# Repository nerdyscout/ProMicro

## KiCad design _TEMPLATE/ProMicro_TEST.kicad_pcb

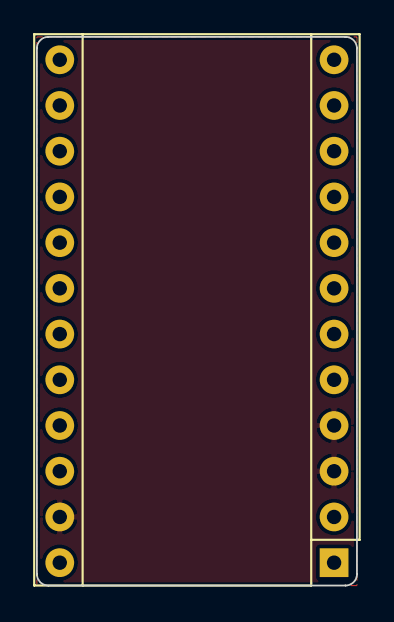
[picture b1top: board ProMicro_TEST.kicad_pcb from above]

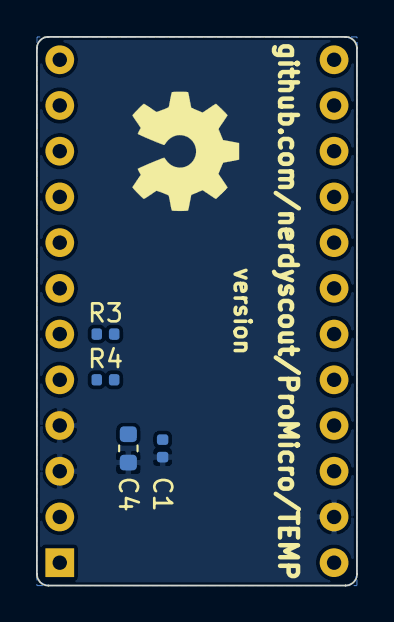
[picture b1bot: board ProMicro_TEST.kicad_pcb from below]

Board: 2 copper layers, 17.8 x 30.5 mm, 6 parts (5 on the bottom side), 4 nets, no tracks yet.

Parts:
A1: Sparkfun_Pro_Micro
C1: 100n; C_0402_1005Metric
C4: 10µ; C_0603_1608Metric
LOGO1: Logo_Open_Hardware_Small; OSHW-Symbol_6.7x6mm_SilkScreen
R3, R4: 4k7; R_0402_1005Metric

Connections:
+3V3: A1.21, C1.1, C4.1, R3.2, R4.2
GND: A1.3, A1.4, A1.23, C1.2, C4.2
SCL: A1.6, R3.1
SDA: A1.5, R4.1

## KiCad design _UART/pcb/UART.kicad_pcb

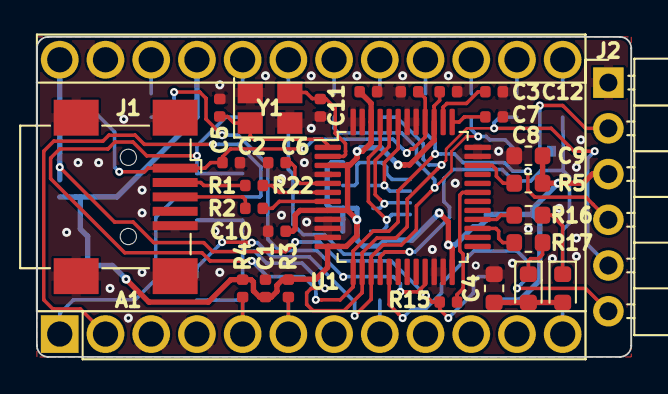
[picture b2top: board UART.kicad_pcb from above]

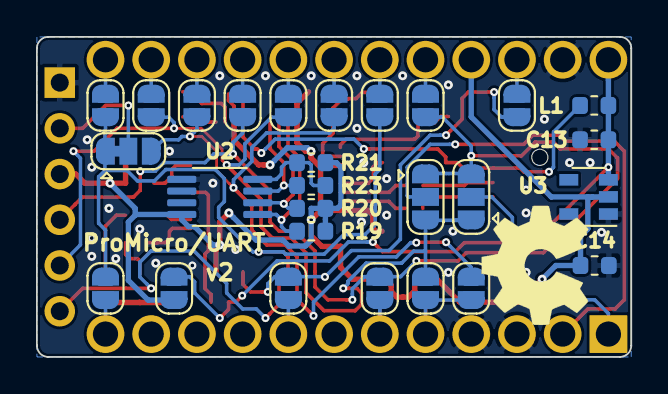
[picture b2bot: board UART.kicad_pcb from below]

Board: 4 copper layers, 33.0 x 17.8 mm, 56 parts (28 on the bottom side), 45 nets.

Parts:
A1: Sparkfun_Pro_Micro_3V3; Sparkfun_Pro_Micro
C1, C3, C7, C8, C10, C11, C12: 100n; C_0402_1005Metric
C2: 4.7µ; C_0402_1005Metric
C4: 10µ; C_0603_1608Metric
C5, C6: 27p; C_0402_1005Metric
C9: 4.7µ; R_0603_1608Metric
C13, C14: 1µ; C_0603_1608Metric
D1: TX; LED_0603_1608Metric
D2: RX; LED_0603_1608Metric
J1: USB_B_Mini; USB_Mini-B_Wuerth_65100516121_Horizontal
J2: Conn_01x06; PinHeader_1x06_P2.54mm_Horizontal
JP1, JP2, JP3, JP4, JP5, JP6, JP7, JP8, JP9, JP12, JP13, JP14, JP15, JP17, JP18: Jumper_NO_Small; SolderJumper-2_P1.3mm_Open_RoundedPad1.0x1.5mm
JP10, JP11: Jumper_3_Bridged12; SolderJumper-3_P1.3mm_Open_RoundedPad1.0x1.5mm
JP16: Jumper_3_Bridged12; SolderJumper-3_P1.3mm_Bridged12_RoundedPad1.0x1.5mm
L1: 0; L_0603_1608Metric
LOGO1: Logo_Open_Hardware_Small; OSHW-Symbol_6.7x6mm_SilkScreen
R1, R2: 22; R_0402_1005Metric
R3, R4: 4k7; R_0402_1005Metric
R5: 1k; R_0603_1608Metric
R15: 39k; R_0402_1005Metric
R16, R17: 220; R_0603_1608Metric
R19, R20, R21: 10k; R_0603_1608Metric
R22: 12k; R_0402_1005Metric
R23: 2k; R_0603_1608Metric
U1: FT232H; LQFP-48_7x7mm_P0.5mm
U2: 93CxxB; MSOP-8_3x3mm_P0.65mm
U3: AZ1117-3.3; SOT-23-5
Y1: 12MHz; Crystal_SMD_3225-4Pin_3.2x2.5mm

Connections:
+3V3: A1.21, C1.1, C4.1, C9.1, C10.2, C11.2, C12.1, C14.1, D1.2, D2.2, J2.3, JP18.2, R3.2, R4.2, R5.2, R19.2, R20.2, R21.2, U1.3, U1.8, U1.12, U1.24, U1.39, U1.46, U2.8, U3.2
+5V: A1.24, C13.1, JP18.1, L1.1, R15.2, U3.3
/CIPO: A1.15, JP3.2
/COPI: A1.14, JP2.2
/CS0: A1.13, JP5.2
/CS1: A1.12, JP4.2
/EECLK: R20.1, U1.44, U2.2
/EECS: R19.1, U1.45, U2.1
/EEDAT: R23.1, U1.43, U2.3
/PWM: A1.8, JP12.2
/RXD: A1.1, JP10.2
/SCK: A1.16, JP1.2
/SCL: A1.6, JP15.2, R3.1
/SDA: A1.5, JP13.2, JP14.2, R4.1
/TCK: A1.20, JP6.2
/TDI: A1.17, JP7.2
/TDO: A1.18, JP8.2
/TMS: A1.19, JP9.2
/TXD: A1.2, JP11.2
/~RST: A1.22, JP17.2
ACBUS0: JP12.1, JP17.1, U1.21
ADBUS0: J2.4, JP1.1, JP6.1, JP10.3, JP11.1, JP15.1, U1.13
ADBUS1: J2.5, JP2.1, JP7.1, JP10.1, JP11.3, JP13.1, U1.14
ADBUS2: JP3.1, JP8.1, JP14.1, JP16.3, U1.15
ADBUS3: JP4.1, JP5.1, JP9.1, JP16.1, U1.16
ADBUS4: J2.6, U1.17
GND: A1.3, A1.4, A1.23, C1.2, C2.2, C3.2, C4.2, C5.2, C6.2, C7.2, C8.2, C9.2, C10.1, C11.1, C12.2, C13.2, C14.2, J1.5, J1.6, J2.1, R22.2, U1.4, U1.9, U1.10, U1.11, U1.22, U1.23, U1.35, U1.36, U1.41, U1.42, U1.47, U1.48, U2.5, U3.1, Y1.2, Y1.4
unnamed: C2.1, C3.1, J1.1, L1.2, U1.40
unnamed: C5.1, U1.1, Y1.1
unnamed: C6.1, U1.2, Y1.3
unnamed: C7.1, U1.38
unnamed: C8.1, U1.37
unnamed: D1.1, R16.2
unnamed: D2.1, R17.2
unnamed: J1.2, R1.2
unnamed: J1.3, R2.2
unnamed: J2.2, JP16.2
unnamed: R1.1, U1.6
unnamed: R2.1, U1.7
unnamed: R5.1, U1.34
unnamed: R21.1, R23.2, U2.4
unnamed: R22.1, U1.5
PWRSAV: R15.1, U1.31
RXLED: R17.1, U1.27
TXLED: R16.1, U1.28

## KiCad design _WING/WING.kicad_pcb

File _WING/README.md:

# ProMicro_WING

## Documentation 
All files can be found on [Github](https://github.com/nerdyscout/ProMicro/tree/master/WING).

### Schematic

### BoM
  * [interactiveHTMLBoM](https://nerdyscout.github.io/ProMicro/WING/docs/bom/WING-ibom.html)
  * [octopart](pcb/docs/bom/WING-bom_octopart.csv)

## Hardware 
### Layout

### Gerbers
can be found within the Github [repository](pcb/gerbers).

## external
### Links
  * [hackaday.io](https://hackaday.io/project/171898-promicro)

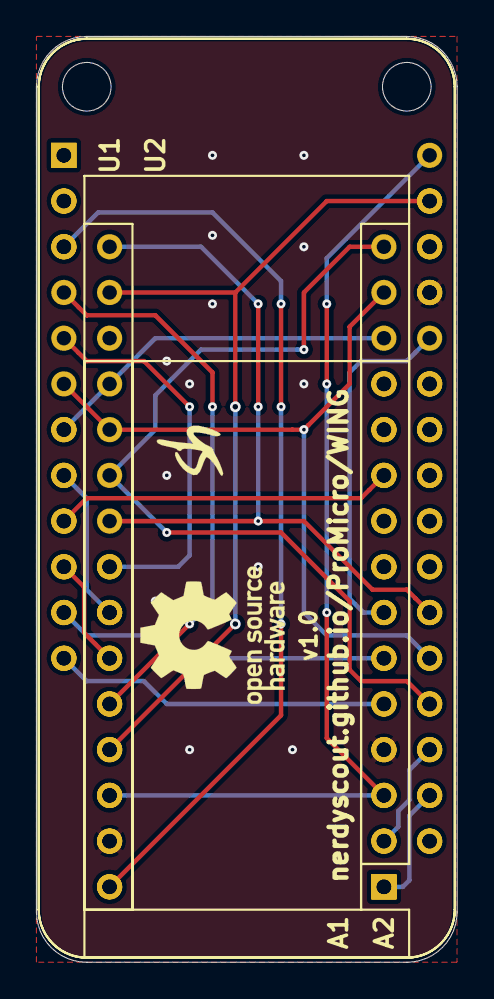
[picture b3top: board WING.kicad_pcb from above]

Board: 2 copper layers, 23.4 x 51.4 mm, 8 parts (0 on the bottom side), 19 nets.

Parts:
A1: Sparkfun_Pro_Micro_3V3; Sparkfun_Pro_Micro
A2: Arduino_Nano_v3.x; Arduino_Nano_mod
LOGO1: Logo_Open_Hardware_Small; OSHW-Logo_7.5x8mm_SilkScreen
TP1, TP2: TestPoint; MountingHole_2.7mm
TP3: initials
U1: Adafruit_HUZZAH32_ESP32_Feather; Adafruit_Feather_mod2
U2: Adafruit_Feather_HUZZAH_ESP8266; Adafruit_Feather

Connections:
+3V3: A1.21, A2.17, A2.27, U1.27, U2.27
+5V: A1.24, U1.3, U2.3
A0: A1.17, U1.5
A1: A1.18, U1.8, U2.8
A2: A1.19, U1.10, U2.10
A3: A1.20, U1.4
D0: A1.2, U1.15, U2.15
D1: A1.1, U1.14, U2.14
D2: A1.5, U1.12, U2.12
D3: A1.6, U1.11, U2.11
D4: A1.7, U2.24
D7: A1.10, U1.9, U2.9
D10: A1.13, U1.7, U2.7
D14: A1.15, U1.16, U2.16
D15: A1.16, U1.18, U2.18
D16: A1.14, U1.6, U1.17, U2.17
EN: U1.2, U2.2
GND: A1.4, A1.23, A2.4, A2.29, U1.25, U2.25
Reset: A1.3, A1.22, A2.3, A2.28, U2.28

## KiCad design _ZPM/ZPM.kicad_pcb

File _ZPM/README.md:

# ProMicro_ZPM 
This module can be mounted to an [Arduino Pro Mini](https://www.sparkfun.com/products/11113), [Arduino Nano](https://store.arduino.cc/arduino-nano), [Sparkfun Pro Micro](https://www.sparkfun.com/products/12587), or any other pincompatible MCU running with 3.3V.

## Documentation
All files can be found on [Github](https://github.com/nerdyscout/ProMicro/tree/master/ZPM).

### Schematic

### BoM
  * [interactiveHTMLBoM](https://nerdyscout.github.io/ProMicro/ZPM/docs/bom/ZPM-ibom.html)
  * [octopart](pcb/docs/bom/ZPM-bom_octopart.csv)

## Hardware 
### Layout

## Gerbers
can be found within the Github [repository](pcb/gerbers).

## external
### Links
  * [hackaday.io](https://hackaday.io/project/171898-promicro)

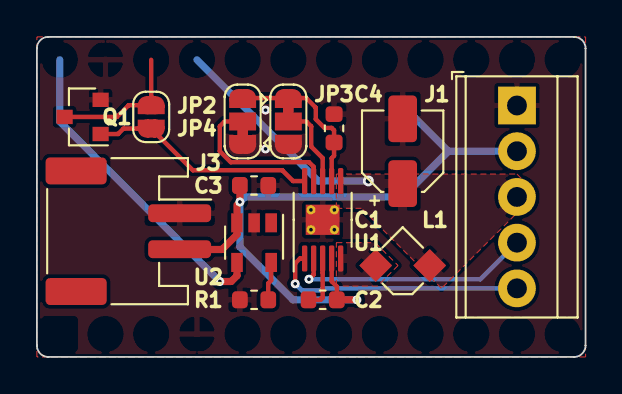
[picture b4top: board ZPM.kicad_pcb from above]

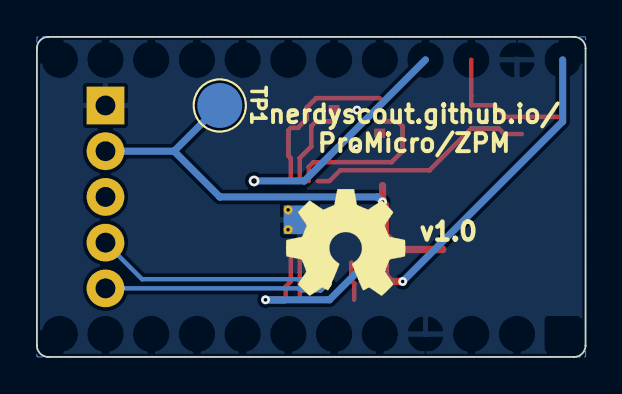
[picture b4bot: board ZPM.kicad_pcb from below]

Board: 2 copper layers, 30.5 x 17.8 mm, 16 parts (2 on the bottom side), 13 nets.

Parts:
C1: 10µF; CP_Elec_4x3
C2: 1µ; C_0603_1608Metric
C3, C4: 4.7µ; C_0603_1608Metric
J1: Screw_Terminal_01x05; TerminalBlock_TE_282834-5_1x05_P2.54mm_Horizontal
J3: JST; JST_PH_S2B-PH-SM4-TB_1x02-1MP_P2.00mm_Horizontal
JP2, JP3: SolderJumper_3_Bridged12; SolderJumper-3_P1.3mm_Bridged12_RoundedPad1.0x1.5mm
JP4: SolderJumper_2_Open; SolderJumper-2_P1.3mm_Open_RoundedPad1.0x1.5mm
L1: CDRH2D18_HPNP-100C; HPNP-100NC
LOGO1: Logo_Open_Hardware_Small; OSHW-Symbol_6.7x6mm_SilkScreen
Q1: BC847; SOT-23
R1: 2k; R_0603_1608Metric
TP1: TestPoint; TestPoint_Pad_D2.5mm
U1: LTC3588EDD-1PBF; MSOP-10-1EP_3x3mm_P0.5mm_EP1.68x1.88mm_ThermalVias
U2: MCP73831-2-OT; SOT-23-5

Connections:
+3V3: C1.1, J1.3, L1.1, U1.6
/D0: JP2.2, U1.9
/D1: JP3.2, U1.8
/Vin2: C4.1, JP2.3, JP3.1, U1.7
GND: C1.2, C3.2, C4.2, J1.1, J3.1, JP2.1, JP3.3, Q1.2, R1.2, U1.11, U2.2
unnamed: C2.1, U1.3
unnamed: J1.4, U1.2
unnamed: J1.5, U1.1
unnamed: JP4.2, Q1.1, U1.10
unnamed: L1.2, U1.5
unnamed: R1.1, U2.5
Reset: JP4.1, Q1.3
VBAT: C2.2, C3.1, J1.2, J3.2, TP1.1, U1.4, U2.3

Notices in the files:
_WING/README.md:
Documentation [![CC BY-SA](../img/ccbysa.png)](pcb/docs/LICENSE.TXT):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
